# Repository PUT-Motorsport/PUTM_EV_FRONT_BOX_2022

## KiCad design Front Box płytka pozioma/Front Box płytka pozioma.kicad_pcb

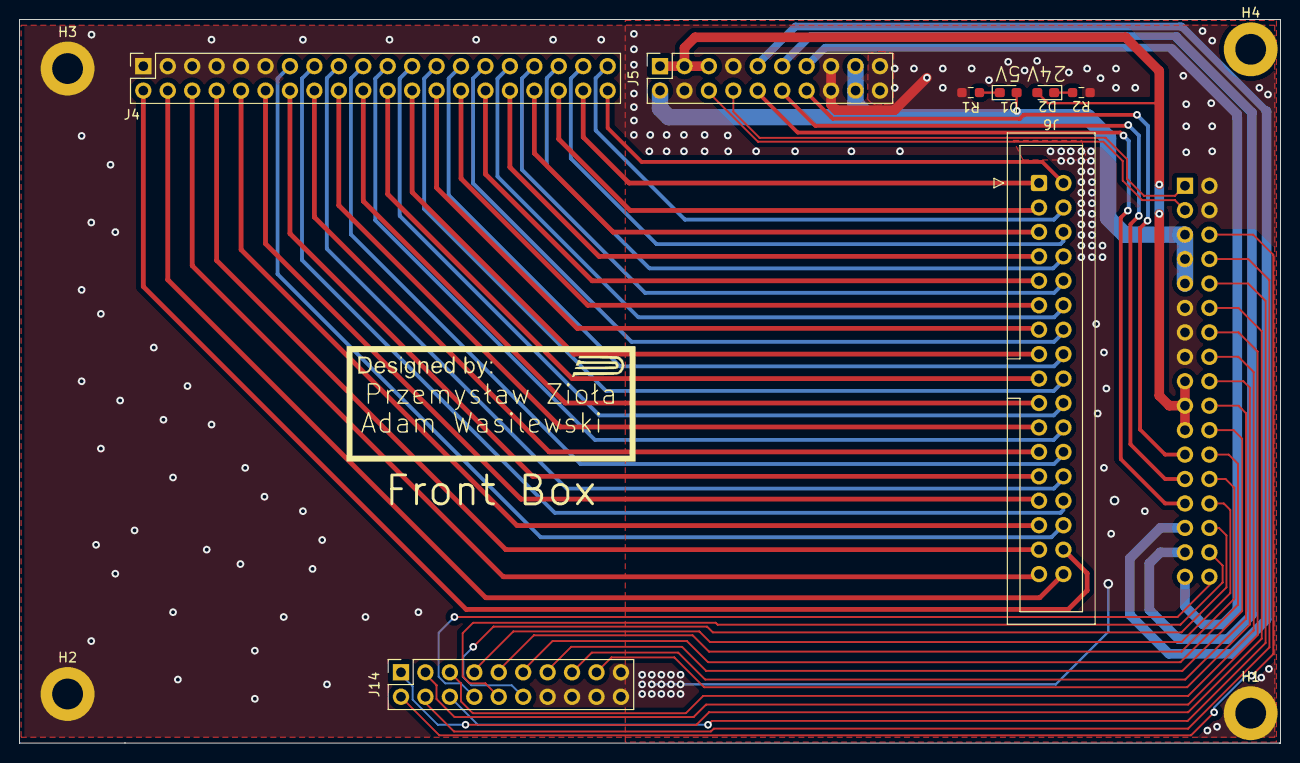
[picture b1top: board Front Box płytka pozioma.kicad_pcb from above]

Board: 4 copper layers, 131.1 x 75.2 mm, 13 parts (1 on the bottom side), 62 nets.

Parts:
D1: 5v indicator; LED_0603_1608Metric_Pad1.05x0.95mm_HandSolder
D2: 24v indicator; LED_0603_1608Metric_Pad1.05x0.95mm_HandSolder
H1, H2, H3, H4: MountingHole_Pad; MountingHole_3.2mm_M3_DIN965_Pad
J4: Sygnały; PinSocket_2x20_P2.54mm_Vertical
J5: Zasilanie+CAN; PinSocket_2x10_P2.54mm_Vertical
J6: Taśma IDC dolna; IDC-Header_2x17_P2.54mm_Vertical
J14: Diagnostyka; PinSocket_2x10_P2.54mm_Vertical
J15: sockety płytka pozioma; PinSocket_2x17_P2.54mm_Vertical
R1, R2: 480R; R_0603_1608Metric_Pad0.98x0.95mm_HandSolder

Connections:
+5V: D1.2 (A), J5.2, J5.17, J5.18, J15.5, J15.7, J15.9
/+24F2: D2.2 (A), J5.1, J5.3, J5.5, J15.17, J15.19, J15.21
/BRAKE_PRESSURE1: J4.12, J6.27
/BRAKE_PRESSURE2: J4.14, J6.25
/BSPD-CURRENT: J4.6, J6.33
/CAN+: J5.6, J15.3
/CAN-: J5.8, J15.1
/CLK1: J14.10, J15.32
/CLK2: J14.9, J15.26
/CLK3: J14.15, J15.20
/CLK4: J14.4, J15.8
/CLK5: J14.3, J15.14
/INERTIA: J4.32, J6.7
/KILL_KIERA: J4.26, J6.13
/KILL_LEWY: J4.30, J6.9
/KILL_PRAWY: J4.28, J6.11
/K_ANALOG0: J4.29, J6.14
/K_OUTPUT0: J4.31, J6.12
/K_OUTPUT1: J4.33, J6.10
/K_OUTPUT2: J4.35, J6.8
/OVERTRAVEL: J4.34, J6.5
/PITOT1: J4.2, J6.32
/PITOT2: J4.4, J6.34
/POT_ZAWIAS2: J4.18, J6.21
/POT_ZAWIAS_1: J4.16, J6.23
/RST1: J14.12, J15.30
/RST2: J14.11, J15.24
/RST3: J14.17, J15.18
/RST4: J14.6, J15.10
/RST5: J14.5, J15.16
/S15: J4.15, J6.28
/S17: J4.17, J6.26
/S19: J4.19, J6.24
/S21: J4.21, J6.22
/S23: J4.23, J6.20
/S25: J4.25, J6.18
/S27: J4.27, J6.16
/S36: J4.36, J6.3
/SAFE-IN: J4.8, J6.31
/SAFE-OUT: J4.10, J6.29
/SIG_APPS1: J4.38, J6.1
/SIG_APPS2: J4.40, J6.2
/SWD1: J14.8, J15.34
/SWD2: J14.7, J15.28
/SWD3: J14.13, J15.22
/SWD4: J14.2, J15.6
/SWD5: J14.1, J15.12
/TEMP1: J4.24, J6.15
/TIM_IN0: J4.37, J6.6
/TIM_IN1: J4.39, J6.4
/WHEELSPEED1: J4.20, J6.19
/WHEELSPEED2: J4.22, J6.17
/WOLNY: J4.13, J6.30
/Z9: J5.9, J15.29
/Z10: J5.10, J15.27
/Z11: J5.11, J15.31
/Z12: J5.12, J15.25
/Z13: J5.13, J15.33
/Z14: J5.14, J15.23
GND: H1.1, H2.1, H3.1, J4.1, J4.3, J4.5, J4.7, J4.9, J4.11, J5.4, J5.7, J5.15, J5.16, J5.19, J5.20, J14.14, J14.16, J14.18, J14.19, J14.20, J15.2, J15.4, J15.11, J15.13, J15.15, R1.1, R2.2
unnamed: D1.1 (K), R1.2
unnamed: D2.1 (K), R2.1

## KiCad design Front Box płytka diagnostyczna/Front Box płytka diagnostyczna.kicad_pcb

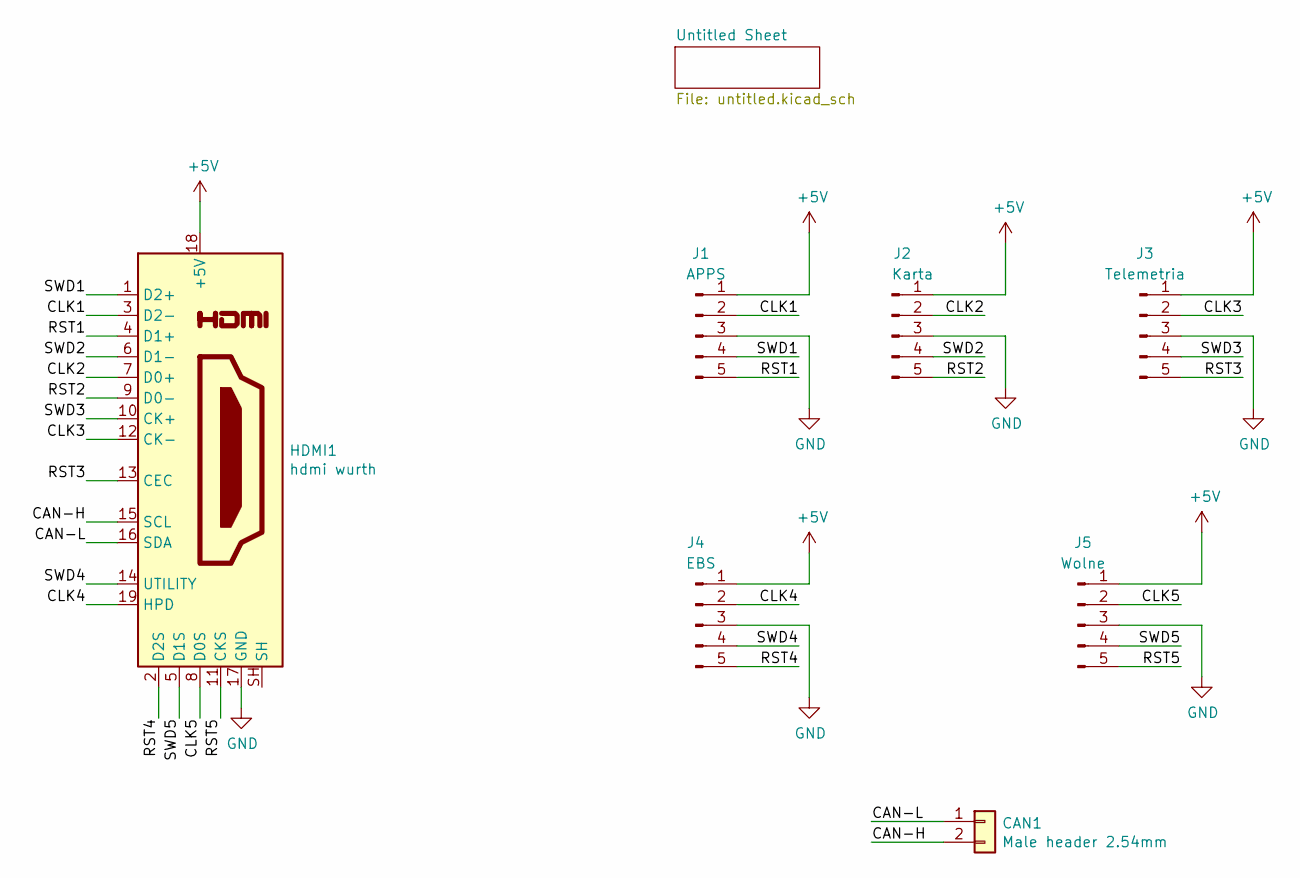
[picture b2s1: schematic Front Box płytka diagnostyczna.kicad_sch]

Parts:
CAN1: Male header 2.54mm; PinHeader_1x02_P2.54mm_Vertical
HDMI1: hdmi wurth; 685119134923
J1: APPS; PinHeader_1x05_P2.54mm_Vertical
J2: Karta; PinHeader_1x05_P2.54mm_Vertical
J3: Telemetria; PinHeader_1x05_P2.54mm_Vertical
J4: EBS; PinHeader_1x05_P2.54mm_Vertical
J5: Wolne; PinHeader_1x05_P2.54mm_Vertical

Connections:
+5V: HDMI1.18 (+5V), J1.1, J2.1, J3.1, J4.1, J5.1
/CAN-H: CAN1.2, HDMI1.15 (SCL)
/CAN-L: CAN1.1, HDMI1.16 (SDA)
/CLK1: HDMI1.3 (D2-), J1.2
/CLK2: HDMI1.7 (D0+), J2.2
/CLK3: HDMI1.12 (CK-), J3.2
/CLK4: HDMI1.19 (HPD), J4.2
/CLK5: HDMI1.8 (D0S), J5.2
/RST1: HDMI1.4 (D1+), J1.5
/RST2: HDMI1.9 (D0-), J2.5
/RST3: HDMI1.13 (CEC), J3.5
/RST4: HDMI1.2 (D2S), J4.5
/RST5: HDMI1.11 (CKS), J5.5
/SWD1: HDMI1.1 (D2+), J1.4
/SWD2: HDMI1.6 (D1-), J2.4
/SWD3: HDMI1.10 (CK+), J3.4
/SWD4: HDMI1.14 (UTILITY), J4.4
/SWD5: HDMI1.5 (D1S), J5.4
GND: HDMI1.17 (GND), J1.3, J2.3, J3.3, J4.3, J5.3

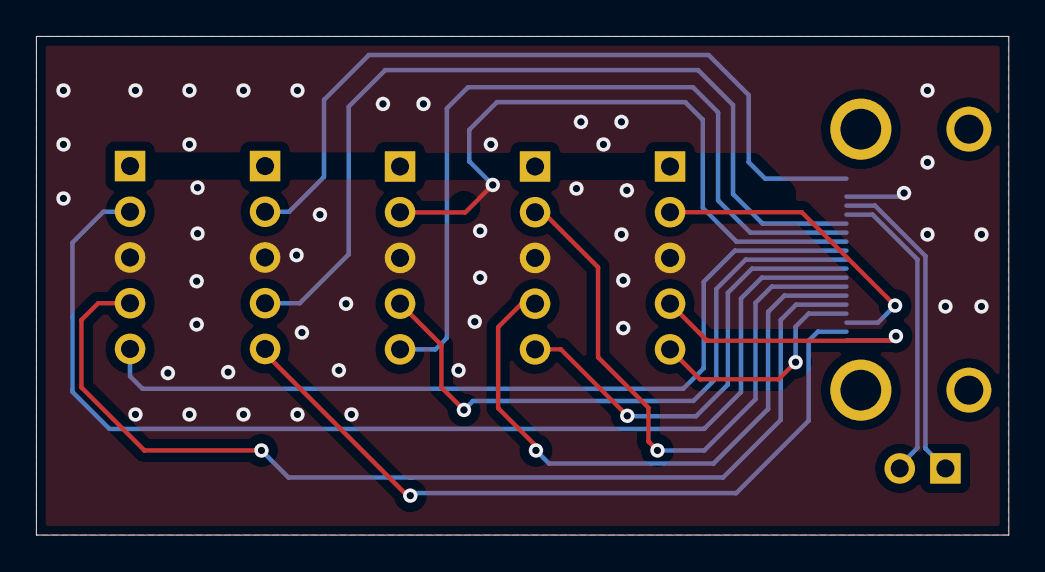
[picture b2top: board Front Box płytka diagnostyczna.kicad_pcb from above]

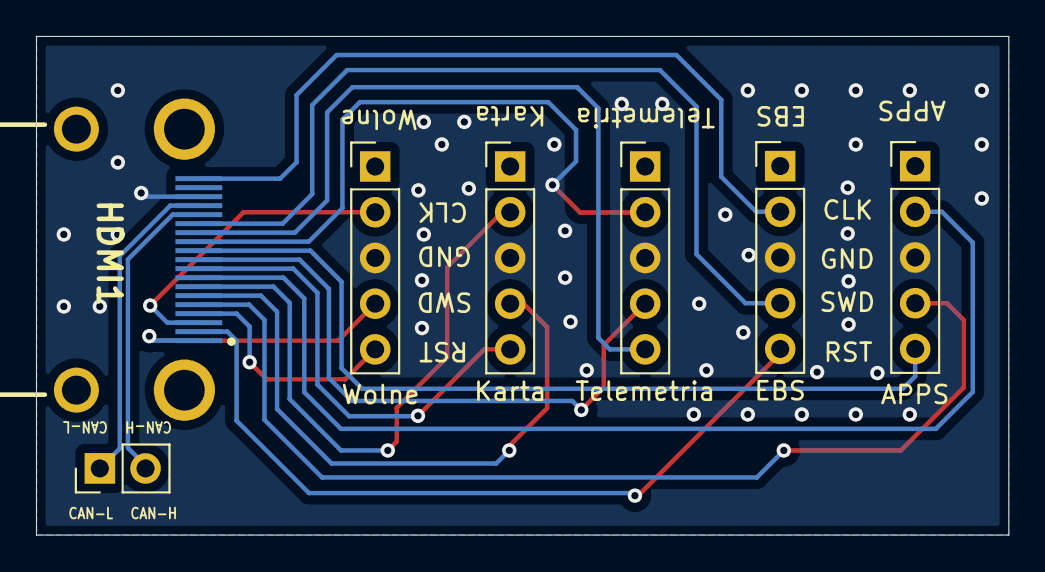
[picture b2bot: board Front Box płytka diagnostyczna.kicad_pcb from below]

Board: 2 copper layers, 54.0 x 27.7 mm, 7 parts (7 on the bottom side), 19 nets.

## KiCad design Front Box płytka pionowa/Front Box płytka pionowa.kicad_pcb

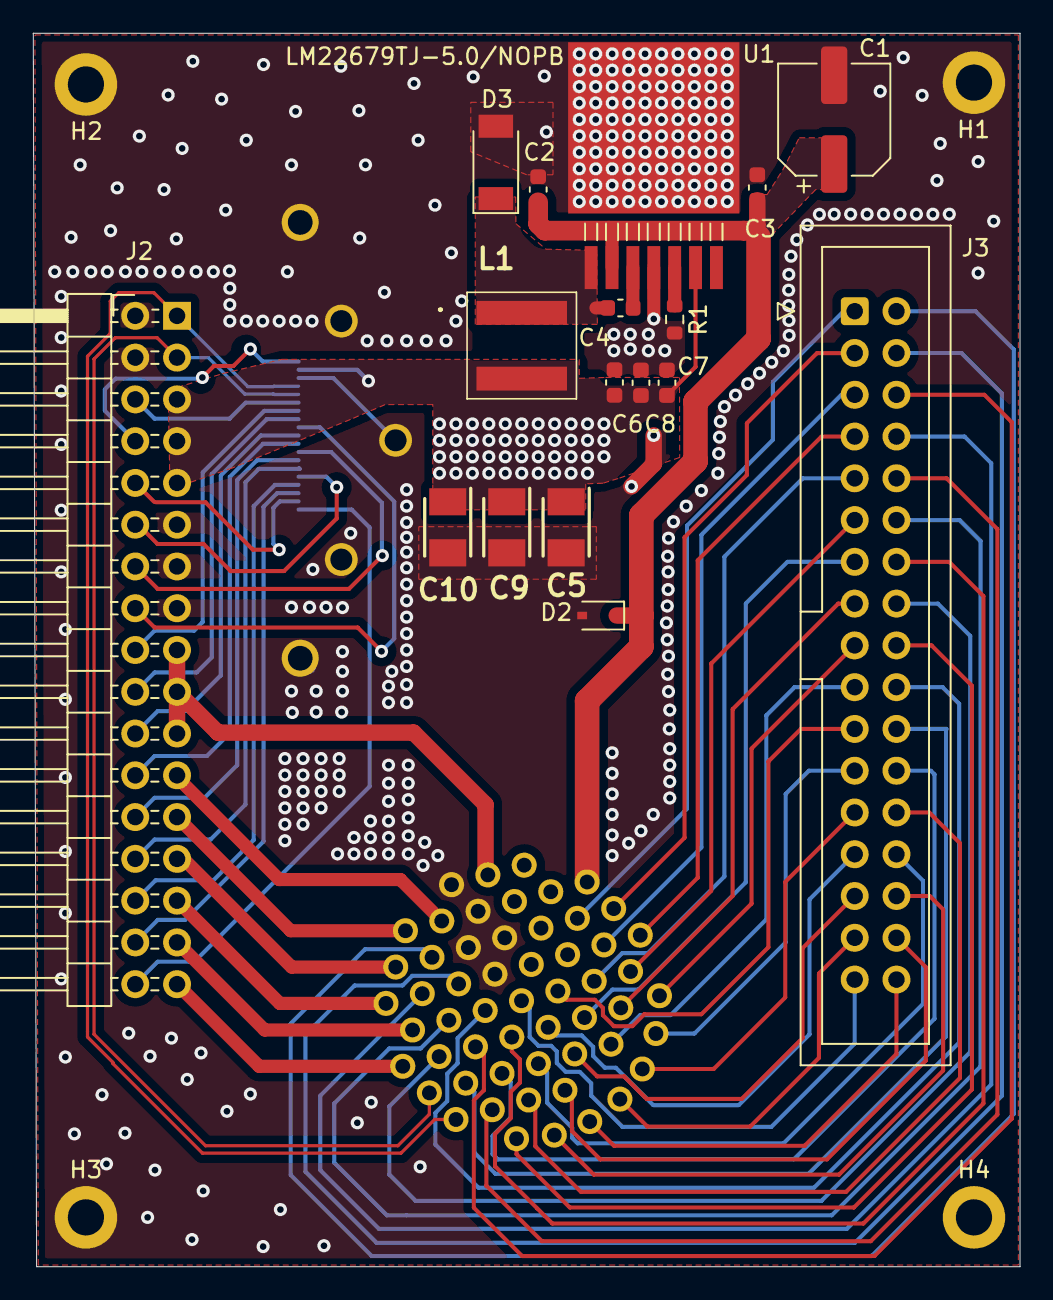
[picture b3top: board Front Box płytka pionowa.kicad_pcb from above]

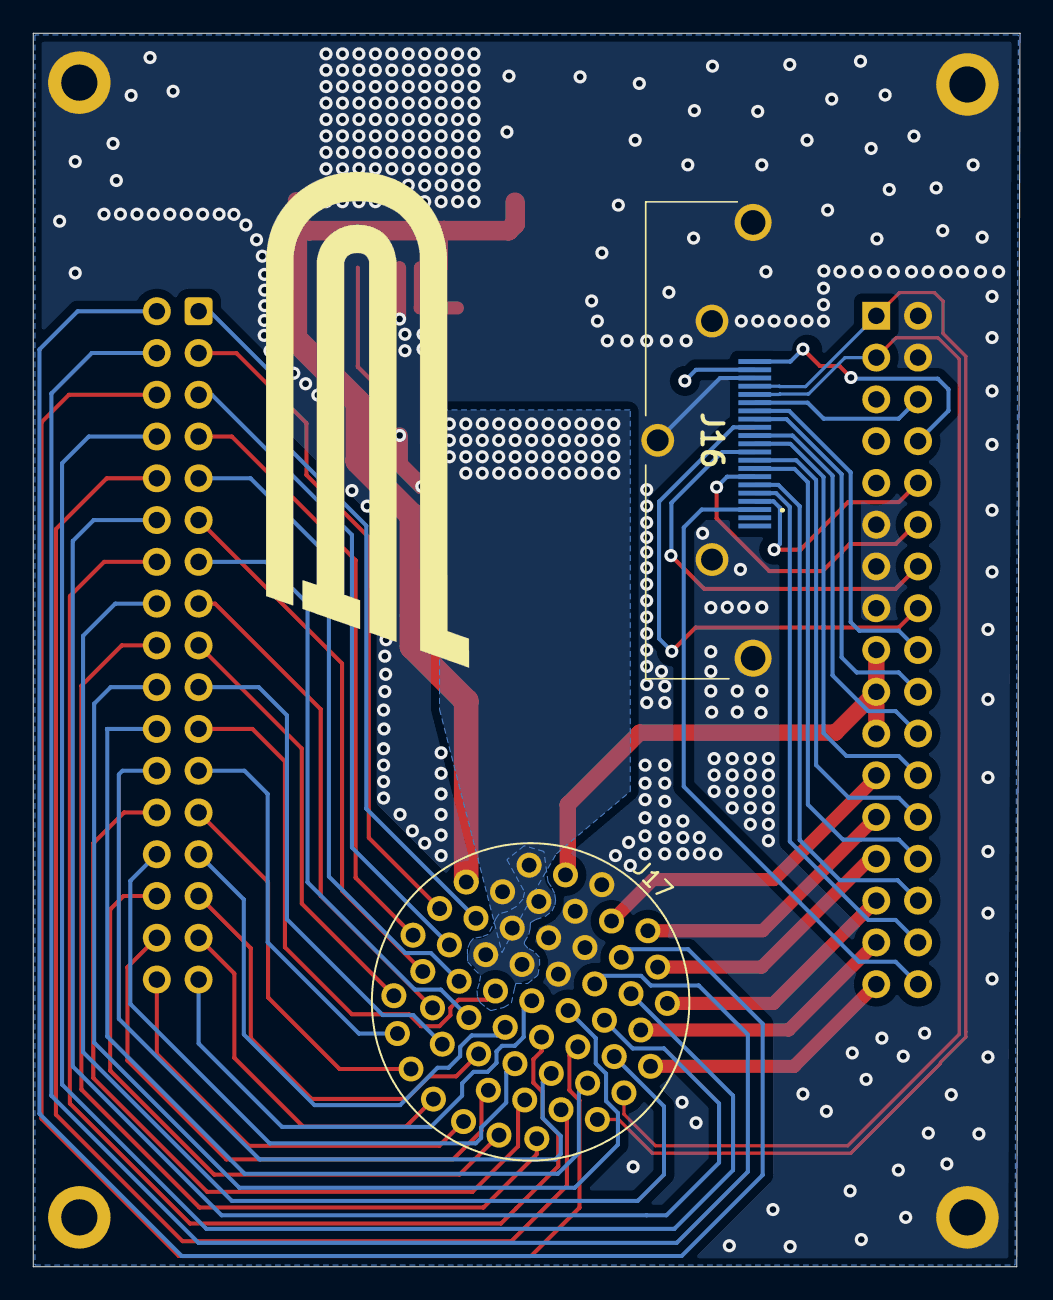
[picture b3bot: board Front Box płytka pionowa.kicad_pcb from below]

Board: 4 copper layers, 60.0 x 75.0 mm, 23 parts (2 on the bottom side), 64 nets.

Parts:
C1: 22uF; CP_Elec_6.3x5.8
C2: 4.7uF; C_0603_1608Metric
C3: 1uF; C_0603_1608Metric
C4: 10nF; C_0603_1608Metric
C5, C9, C10: 68uF; CAPPM3528X210N
C6, C7, C8: 100nF; C_0603_1608Metric
D2: SD36_SOD323; D_SOD-323
D3: Schottky 60V 5A; D_SOD-128
H1, H2, H3, H4: MountingHole_Pad; MountingHole_2.2mm_M2_DIN965_Pad
J2: piny kątowe; PinHeader_2x17_P2.54mm_Horizontal
J3: Taśma IDC góra; IDC-Header_2x17_P2.54mm_Vertical
J16: hdmi diagnostyka; SS53000003
J17: Złącze TE; TE-AUTOSPORT-16-36
L1: 6.8uH; 74439346068
R1: 9k; R_0603_1608Metric
U1: LM22679TJ-5.0/NOPB; LM22679TJ-5.0&slash_NOPB

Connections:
+5V: C5.1, C6.1, C7.1, C8.1, C9.1, C10.1, J2.5, J2.7, J2.9, J16.18 (+5V), J17.8, J17.9, J17.13, J17.14, J17.15, J17.21, L1.2, U1.6 (FB)
/+24F1: C1.1, C2.1, C3.1, D2.1 (A1), J17.3, U1.2 (VIN)
/płytka pionowa/+24F2: J2.17, J2.19, J2.21, J17.16
/płytka pionowa/BRAKE_PRESSURE1: J3.27, J17.27
/płytka pionowa/BRAKE_PRESSURE2: J3.25, J17.17
/płytka pionowa/BSPD-CURRENT: J3.33, J17.28
/płytka pionowa/CAN+: J2.3, J16.15 (SCL), J17.54
/płytka pionowa/CAN-: J2.1, J16.16 (SDA), J17.53
/płytka pionowa/CLK1: J2.32, J16.3 (D2-)
/płytka pionowa/CLK2: J2.26, J16.7 (D0+)
/płytka pionowa/CLK3: J2.20, J16.12 (CK-)
/płytka pionowa/CLK4: J2.8, J16.19 (HPD)
/płytka pionowa/CLK5: J2.14, J16.8 (D0S)
/płytka pionowa/INERTIA: J3.7, J17.1
/płytka pionowa/KILL_KIERA: J3.13, J17.19
/płytka pionowa/KILL_LEWY: J3.9, J17.12
/płytka pionowa/KILL_PRAWY: J3.11, J17.5
/płytka pionowa/K_ANALOG0: J3.14, J17.35
/płytka pionowa/K_OUTPUT0: J3.12, J17.44
/płytka pionowa/K_OUTPUT1: J3.10, J17.48
/płytka pionowa/K_OUTPUT2: J3.8, J17.45
/płytka pionowa/OVERTRAVEL: J3.5, J17.6
/płytka pionowa/PITOT1: J3.32, J17.33
/płytka pionowa/PITOT2: J3.34, J17.32
/płytka pionowa/POT_ZAWIAS2: J3.21, J17.20
/płytka pionowa/POT_ZAWIAS_1: J3.23, J17.10
/płytka pionowa/RST1: J2.30, J16.4 (D1+)
/płytka pionowa/RST2: J2.24, J16.9 (D0-)
/płytka pionowa/RST3: J2.18, J16.13 (CEC)
/płytka pionowa/RST4: J2.10, J16.2 (D2S)
/płytka pionowa/RST5: J2.16, J16.11 (CKS)
/płytka pionowa/S15: J3.28, J17.34
/płytka pionowa/S17: J3.26, J17.41
/płytka pionowa/S19: J3.24, J17.42
/płytka pionowa/S21: J3.22, J17.49
/płytka pionowa/S23: J3.20, J17.36
/płytka pionowa/S25: J3.18, J17.47
/płytka pionowa/S27: J3.16, J17.50
/płytka pionowa/S36: J3.3, J17.2
/płytka pionowa/SAFE-IN: J3.31, J17.25
/płytka pionowa/SAFE-OUT: J3.29, J17.26
/płytka pionowa/SIG_APPS1: J3.1, J17.7
/płytka pionowa/SIG_APPS2: J3.2, J17.38
/płytka pionowa/SWD1: J2.34, J16.1 (D2+)
/płytka pionowa/SWD2: J2.28, J16.6 (D1-)
/płytka pionowa/SWD3: J2.22, J16.10 (CK+)
/płytka pionowa/SWD4: J2.6, J16.14 (UTILITY)
/płytka pionowa/SWD5: J2.12, J16.5 (D1S)
/płytka pionowa/TEMP1: J3.15, J17.11
/płytka pionowa/TIM_IN0: J3.6, J17.43
/płytka pionowa/TIM_IN1: J3.4, J17.37
/płytka pionowa/WHEELSPEED1: J3.19, J17.18
/płytka pionowa/WHEELSPEED2: J3.17, J17.4
/płytka pionowa/WOLNY: J3.30, J17.40
/płytka pionowa/Z9: J2.29, J17.52
/płytka pionowa/Z10: J2.27, J17.46
/płytka pionowa/Z11: J2.31, J17.51
/płytka pionowa/Z12: J2.25, J17.39
/płytka pionowa/Z13: J2.33, J17.55
/płytka pionowa/Z14: J2.23, J17.31
GND: C1.2, C2.2, C3.2, C5.2, C6.2, C7.2, C8.2, C9.2, C10.2, D2.2 (A2), D3.2 (A), H1.1, H2.1, H3.1, J2.2, J2.4, J2.11, J2.13, J2.15, J16.17 (GND), J16.SH, J17.22, J17.23, J17.24, J17.29, J17.30, R1.2, U1.4 (GND), U1.8 (DAP)
unnamed: C4.1, D3.1 (K), L1.1, U1.1 (SW)
unnamed: C4.2, U1.3 (BOOT)
unnamed: R1.1, U1.5 (IADJ)

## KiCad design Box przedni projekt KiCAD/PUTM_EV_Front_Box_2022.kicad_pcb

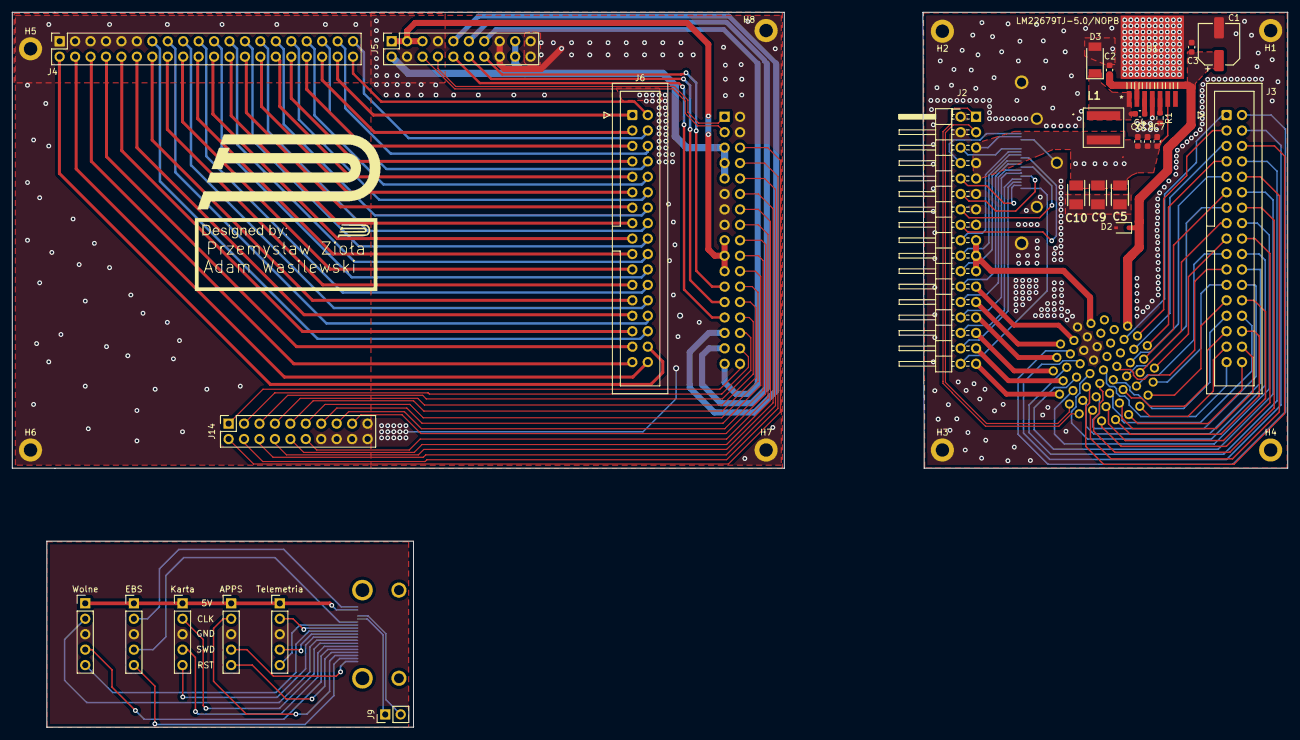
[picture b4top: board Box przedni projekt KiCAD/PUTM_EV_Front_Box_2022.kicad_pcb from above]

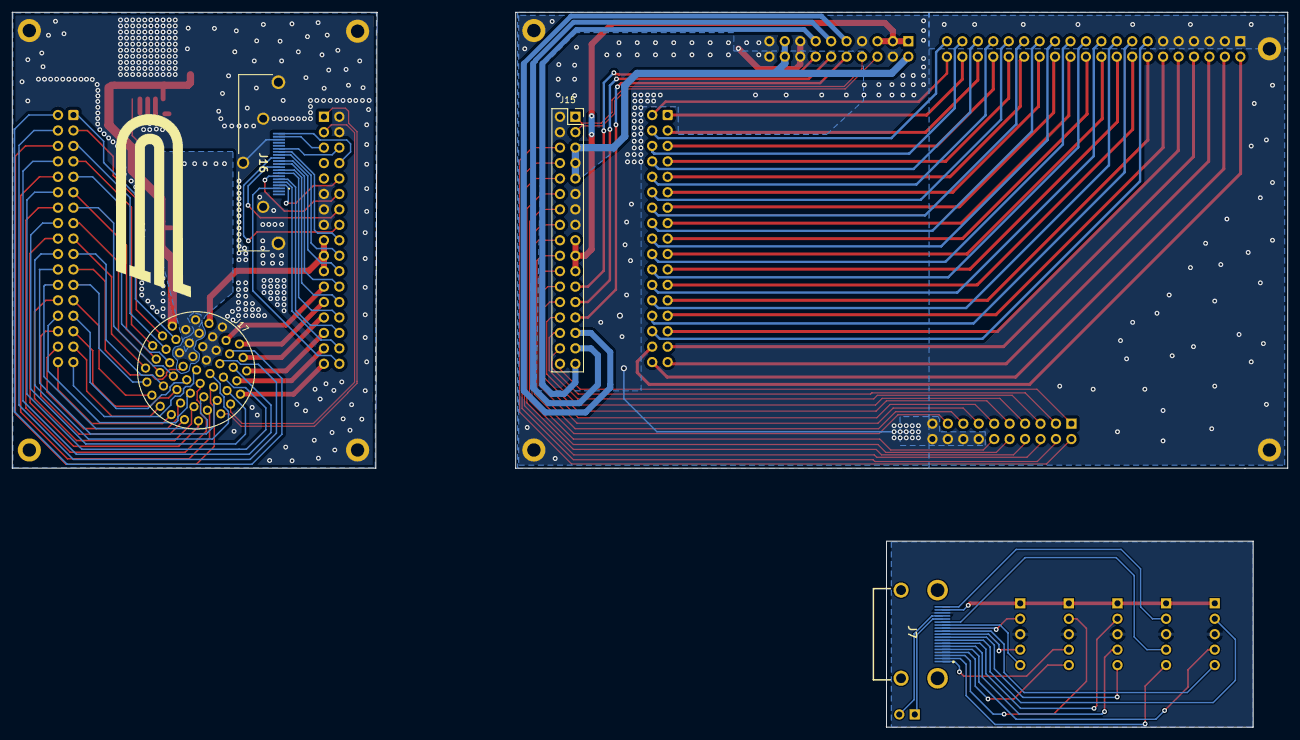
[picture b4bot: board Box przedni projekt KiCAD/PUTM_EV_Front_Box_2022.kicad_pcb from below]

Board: 2 copper layers, 209.8 x 117.6 mm, 39 parts (4 on the bottom side), 139 nets.

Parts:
APPS: 4; PinHeader_1x05_P2.54mm_Vertical
C1: 22uF; CP_Elec_6.3x5.8
C2: 4.7uF; C_0603_1608Metric
C3: 1uF; C_0603_1608Metric
C4: 10nF; C_0603_1608Metric
C5, C9, C10: 68uF; CAPPM3528X210N
C6, C7, C8: 100nF; C_0603_1608Metric
D2: SD36_SOD323; D_SOD-323
D3: Schottky 60V 5A; D_SOD-128
EBS: 2; PinHeader_1x05_P2.54mm_Vertical
H1, H2, H3, H4, H5, H6, H7, H8: MountingHole_Pad; MountingHole_2.2mm_M2_DIN965_Pad
J2: piny kątowe; PinHeader_2x17_P2.54mm_Horizontal
J3: Taśma IDC góra; IDC-Header_2x17_P2.54mm_Vertical
J4: Sygnały; PinSocket_2x20_P2.54mm_Vertical
J5: Zasilanie+CAN; PinSocket_2x10_P2.54mm_Vertical
J6: Taśma IDC dolna; IDC-Header_2x17_P2.54mm_Vertical
J7: hdmi wurth; 685119134923
J9: Conn_01x02; PinHeader_1x02_P2.54mm_Vertical
J14: Diagnostyka; PinSocket_2x10_P2.54mm_Vertical
J15: sockety płytka pozioma; PinSocket_2x17_P2.54mm_Vertical
J16: hdmi diagnostyka; SS53000003
J17: Złącze TE; TE-AUTOSPORT-16-36
Karta: 3; PinHeader_1x05_P2.54mm_Vertical
L1: 6.8uH; 74439346068
R1: 9k; R_0603_1608Metric
Telemetria: 5; PinHeader_1x05_P2.54mm_Vertical
U1: LM22679TJ-5.0/NOPB; LM22679TJ-5.0&slash_NOPB
Wolne: 1; PinHeader_1x05_P2.54mm_Vertical

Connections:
+5V: APPS.1, C5.1, C6.1, C7.1, C8.1, C9.1, C10.1, EBS.1, J2.5, J2.7, J2.9, J5.2, J5.17, J5.18, J7.18 (+5V), J15.5, J15.7, J15.9, J16.18 (+5V), J17.8, J17.9, J17.13, J17.14, J17.15, J17.21, Karta.1, L1.2, Telemetria.1, U1.6 (FB), Wolne.1
/+24F1: C1.1, C2.1, C3.1, D2.1 (A1), J17.3, U1.2 (VIN)
/+24F2: J5.1, J5.3, J5.5, J15.17, J15.19, J15.21
/BRAKE_PRESSURE1: J4.12, J6.27
/BRAKE_PRESSURE2: J4.14, J6.25
/BSPD-CURRENT: J4.6, J6.33
/CAN+: J5.6, J15.3
/CAN-: J5.8, J15.1
/CLK1: J14.3, J15.32
/CLK2: J14.9, J15.26
/CLK3: J14.15, J15.20
/CLK4: J14.4, J15.8
/CLK5: J14.10, J15.14
/INERTIA: J4.32, J6.7
/KILL_KIERA: J4.26, J6.13
/KILL_LEWY: J4.30, J6.9
/KILL_PRAWY: J4.28, J6.11
/K_ANALOG0: J4.29, J6.14
/K_OUTPUT0: J4.31, J6.12
/K_OUTPUT1: J4.33, J6.10
/K_OUTPUT2: J4.35, J6.8
/OVERTRAVEL: J4.34, J6.5
/PITOT1: J4.2, J6.32
/PITOT2: J4.4, J6.34
/POT_ZAWIAS2: J4.18, J6.21
/POT_ZAWIAS_1: J4.16, J6.23
/RST1: J14.5, J15.30
/RST2: J14.11, J15.24
/RST3: J14.17, J15.18
/RST4: J14.6, J15.10
/RST5: J14.12, J15.16
/S15: J4.15, J6.28
/S17: J4.17, J6.26
/S19: J4.19, J6.24
/S21: J4.21, J6.22
/S23: J4.23, J6.20
/S25: J4.25, J6.18
/S27: J4.27, J6.16
/S36: J4.36, J6.3
/SAFE-IN: J4.8, J6.31
/SAFE-OUT: J4.10, J6.29
/SIG_APPS1: J4.38, J6.1
/SIG_APPS2: J4.40, J6.2
/SWD1: J14.1, J15.34
/SWD2: J14.7, J15.28
/SWD3: J14.13, J15.22
/SWD4: J14.2, J15.6
/SWD5: J14.8, J15.12
/TEMP1: J4.24, J6.15
/TIM_IN0: J4.37, J6.6
/TIM_IN1: J4.39, J6.4
/WHEELSPEED1: J4.20, J6.19
/WHEELSPEED2: J4.22, J6.17
/WOLNY: J4.13, J6.30
/Z9: J5.9, J15.29
/Z10: J5.10, J15.27
/Z11: J5.11, J15.31
/Z12: J5.12, J15.25
/Z13: J5.13, J15.33
/Z14: J5.14, J15.23
/goldpin-hdmi/CAN-H: J7.15 (SCL), J9.1
/goldpin-hdmi/CAN-L: J7.16 (SDA), J9.2
/goldpin-hdmi/CLK1: APPS.2, J7.3 (D2-)
/goldpin-hdmi/CLK2: J7.7 (D0+), Karta.2
/goldpin-hdmi/CLK3: J7.12 (CK-), Telemetria.2
/goldpin-hdmi/CLK4: EBS.2, J7.19 (HPD)
/goldpin-hdmi/CLK5: J7.8 (D0S), Wolne.2
/goldpin-hdmi/RST1: APPS.5, J7.4 (D1+)
/goldpin-hdmi/RST2: J7.9 (D0-), Karta.5
/goldpin-hdmi/RST3: J7.13 (CEC), Telemetria.5
/goldpin-hdmi/RST4: EBS.5, J7.2 (D2S)
/goldpin-hdmi/RST5: J7.11 (CKS), Wolne.5
/goldpin-hdmi/SWD1: APPS.4, J7.1 (D2+)
/goldpin-hdmi/SWD2: J7.6 (D1-), Karta.4
/goldpin-hdmi/SWD3: J7.10 (CK+), Telemetria.4
/goldpin-hdmi/SWD4: EBS.4, J7.14 (UTILITY)
/goldpin-hdmi/SWD5: J7.5 (D1S), Wolne.4
/płytka pionowa/+24F2: J2.17, J2.19, J2.21, J17.16
/płytka pionowa/BRAKE_PRESSURE1: J3.27, J17.27
/płytka pionowa/BRAKE_PRESSURE2: J3.25, J17.17
/płytka pionowa/BSPD-CURRENT: J3.33, J17.28
/płytka pionowa/CAN+: J2.3, J17.54
/płytka pionowa/CAN-: J2.1, J17.53
/płytka pionowa/CLK1: J2.32, J16.3 (D2-)
/płytka pionowa/CLK2: J2.26, J16.7 (D0+)
/płytka pionowa/CLK3: J2.20, J16.12 (CK-)
/płytka pionowa/CLK4: J2.8, J16.19 (HPD)
/płytka pionowa/CLK5: J2.14, J16.8 (D0S)
/płytka pionowa/INERTIA: J3.7, J17.1
/płytka pionowa/KILL_KIERA: J3.13, J17.19
/płytka pionowa/KILL_LEWY: J3.9, J17.12
/płytka pionowa/KILL_PRAWY: J3.11, J17.5
/płytka pionowa/K_ANALOG0: J3.14, J17.35
/płytka pionowa/K_OUTPUT0: J3.12, J17.44
/płytka pionowa/K_OUTPUT1: J3.10, J17.48
/płytka pionowa/K_OUTPUT2: J3.8, J17.45
/płytka pionowa/OVERTRAVEL: J3.5, J17.6
/płytka pionowa/PITOT1: J3.32, J17.33
/płytka pionowa/PITOT2: J3.34, J17.32
/płytka pionowa/POT_ZAWIAS2: J3.21, J17.20
/płytka pionowa/POT_ZAWIAS_1: J3.23, J17.10
/płytka pionowa/RST1: J2.30, J16.4 (D1+)
/płytka pionowa/RST2: J2.24, J16.9 (D0-)
/płytka pionowa/RST3: J2.18, J16.13 (CEC)
/płytka pionowa/RST4: J2.10, J16.2 (D2S)
/płytka pionowa/RST5: J2.16, J16.11 (CKS)
/płytka pionowa/S15: J3.28, J17.34
/płytka pionowa/S17: J3.26, J17.41
/płytka pionowa/S19: J3.24, J17.42
/płytka pionowa/S21: J3.22, J17.49
/płytka pionowa/S23: J3.20, J17.36
/płytka pionowa/S25: J3.18, J17.47
/płytka pionowa/S27: J3.16, J17.50
/płytka pionowa/S36: J3.3, J17.2
/płytka pionowa/SAFE-IN: J3.31, J17.25
/płytka pionowa/SAFE-OUT: J3.29, J17.26
/płytka pionowa/SIG_APPS1: J3.1, J17.7
/płytka pionowa/SIG_APPS2: J3.2, J17.38
/płytka pionowa/SWD1: J2.34, J16.1 (D2+)
/płytka pionowa/SWD2: J2.28, J16.6 (D1-)
/płytka pionowa/SWD3: J2.22, J16.10 (CK+)
/płytka pionowa/SWD4: J2.6, J16.14 (UTILITY)
/płytka pionowa/SWD5: J2.12, J16.5 (D1S)
/płytka pionowa/TEMP1: J3.15, J17.11
/płytka pionowa/TIM_IN0: J3.6, J17.43
/płytka pionowa/TIM_IN1: J3.4, J17.37
/płytka pionowa/WHEELSPEED1: J3.19, J17.18
/płytka pionowa/WHEELSPEED2: J3.17, J17.4
/płytka pionowa/WOLNY: J3.30, J17.40
/płytka pionowa/Z9: J2.29, J17.52
/płytka pionowa/Z10: J2.27, J17.46
/płytka pionowa/Z11: J2.31, J17.51
/płytka pionowa/Z12: J2.25, J17.39
/płytka pionowa/Z13: J2.33, J17.55
/płytka pionowa/Z14: J2.23, J17.31
GND: APPS.3, C1.2, C2.2, C3.2, C5.2, C6.2, C7.2, C8.2, C9.2, C10.2, D2.2 (A2), D3.2 (A), EBS.3, H1.1, H2.1, H3.1, H5.1, H6.1, H7.1, H8.1, J2.2, J2.4, J2.11, J2.13, J2.15, J4.1, J4.3, J4.5, J4.7, J4.9, J4.11, J5.4, J5.7, J5.15, J5.16, J5.19, J5.20, J7.17 (GND), J14.14, J14.16, J14.18, J14.19, J14.20, J15.2, J15.4, J15.11, J15.13, J15.15, J16.17 (GND), J16.SH, J17.22, J17.23, J17.24, J17.29, J17.30, Karta.3, R1.2, Telemetria.3, U1.4 (GND), U1.8 (DAP), Wolne.3
unnamed: C4.1, D3.1 (K), L1.1, U1.1 (SW)
unnamed: C4.2, U1.3 (BOOT)
unnamed: R1.1, U1.5 (IADJ)

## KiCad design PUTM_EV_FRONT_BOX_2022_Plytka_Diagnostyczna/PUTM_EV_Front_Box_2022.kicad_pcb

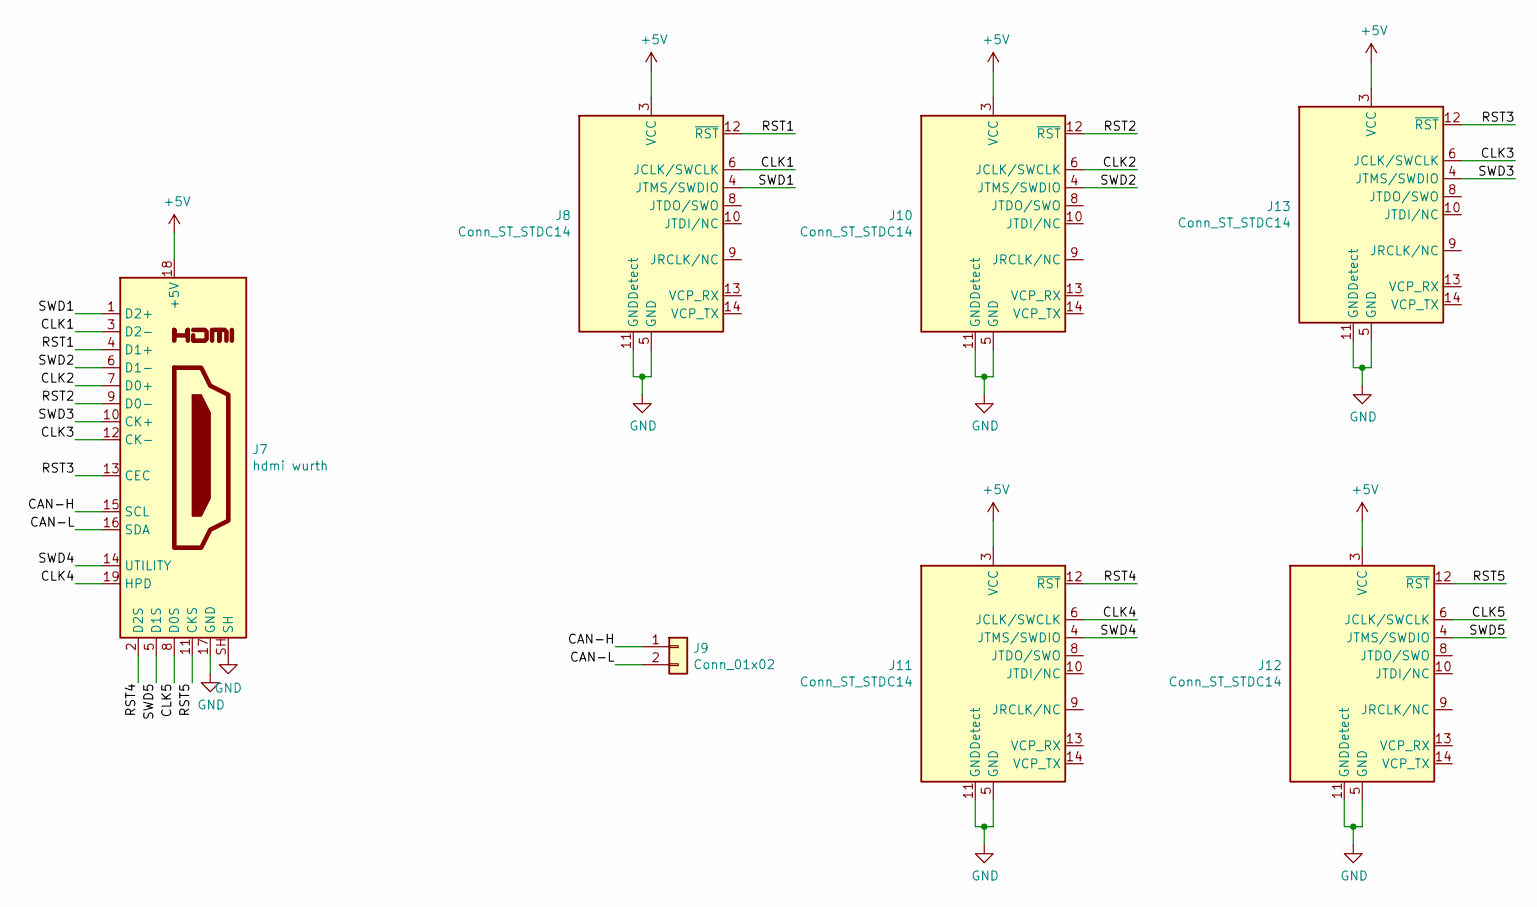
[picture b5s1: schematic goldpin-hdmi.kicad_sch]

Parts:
J7: hdmi wurth; 685119134923
J8, J10, J11, J12, J13: Conn_ST_STDC14; PinHeader_2x07_P2.54mm_Vertical
J9: Conn_01x02; PinHeader_1x02_P2.54mm_Vertical

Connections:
+5V: J7.18 (+5V), J8.3 (VCC), J10.3 (VCC), J11.3 (VCC), J12.3 (VCC), J13.3 (VCC)
/goldpin-hdmi/CAN-H: J7.15 (SCL), J9.1
/goldpin-hdmi/CAN-L: J7.16 (SDA), J9.2
/goldpin-hdmi/CLK1: J7.3 (D2-), J8.6 (JCLK/SWCLK)
/goldpin-hdmi/CLK2: J7.7 (D0+), J10.6 (JCLK/SWCLK)
/goldpin-hdmi/CLK3: J7.12 (CK-), J13.6 (JCLK/SWCLK)
/goldpin-hdmi/CLK4: J7.19 (HPD), J11.6 (JCLK/SWCLK)
/goldpin-hdmi/CLK5: J7.8 (D0S), J12.6 (JCLK/SWCLK)
/goldpin-hdmi/RST1: J7.4 (D1+), J8.12 (~RST)
/goldpin-hdmi/RST2: J7.9 (D0-), J10.12 (~RST)
/goldpin-hdmi/RST3: J7.13 (CEC), J13.12 (~RST)
/goldpin-hdmi/RST4: J7.2 (D2S), J11.12 (~RST)
/goldpin-hdmi/RST5: J7.11 (CKS), J12.12 (~RST)
/goldpin-hdmi/SWD1: J7.1 (D2+), J8.4 (JTMS/SWDIO)
/goldpin-hdmi/SWD2: J7.6 (D1-), J10.4 (JTMS/SWDIO)
/goldpin-hdmi/SWD3: J7.10 (CK+), J13.4 (JTMS/SWDIO)
/goldpin-hdmi/SWD4: J7.14 (UTILITY), J11.4 (JTMS/SWDIO)
/goldpin-hdmi/SWD5: J7.5 (D1S), J12.4 (JTMS/SWDIO)
GND: J7.17 (GND), J7.20, J7.21, J7.22, J7.23, J8.5 (GND), J8.7 (GND), J8.11 (GNDDetect), J10.5 (GND), J10.7 (GND), J10.11 (GNDDetect), J11.5 (GND), J11.7 (GND), J11.11 (GNDDetect), J12.5 (GND), J12.7 (GND), J12.11 (GNDDetect), J13.5 (GND), J13.7 (GND), J13.11 (GNDDetect)

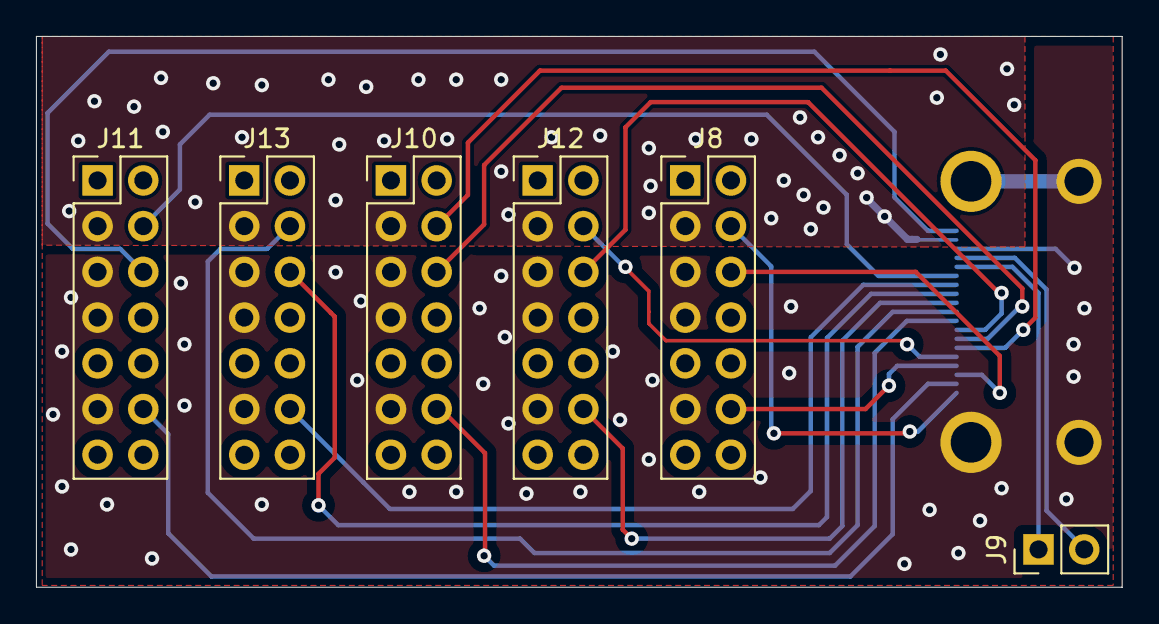
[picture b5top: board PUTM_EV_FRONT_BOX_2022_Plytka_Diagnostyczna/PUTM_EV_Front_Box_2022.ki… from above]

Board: 2 copper layers, 60.3 x 30.6 mm, 7 parts (1 on the bottom side), 19 nets.

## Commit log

2022-01-23 preproduction review small bug fixes
2022-01-23 Minor changes
2022-01-24 Final changes
2022-01-24 New plains in diagnostyka
2022-01-24 New Plains
2022-02-10 Added article
2022-04-06 Separated boards into individual projects
2022-04-06 New silkscreen and connectors for diagnostic board
2022-04-08 PCB prepared for gerber generation
2022-04-08 Added missing traces
2022-04-08 Even better silkscreen for diagnostic PCB
2022-06-14 quick revision
    Added LED's to horizontal board, distance between sockets fix, Diagnostic Board 5v line delete and compatibility with HDMI fix
2022-06-23 Changed mounting holes to M3 size because Maciej was crying a lot

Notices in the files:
parts and their libraries:
Copyright 2021 Accelerated Designs. All rights reserved.
